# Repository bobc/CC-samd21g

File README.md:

CC-samd21g Breakout Board
========================================

The CC-SAMD21 Breakout Board is breakout for the Atmel ATSAMD21G18 with prototyping area.  
This board shape is dirfferent from Arduino UNO or Zero, but it has Arduino Uno V3 style headers.  
There are only the minimal set of parts for running microcontroller. When you make your own circuit boards, this board might be helpful.

### Some highlights of the CC-samd21g Breakout Board:
 1. Main core: [ATSAMD21G18](http://www.atmel.com/devices/ATSAMD21G18A.aspx)
 2. Volatage regulator can be mounted in the extra prototyping area.
 3. Prototyping area 43.94mm(1730mil) x 53.34mm(2100mil)
 4. Measures 99.82mm(3930mil) x 53.34mm(2100mil)

Repository Contents
-------------------
* **/Hardware** - All Eagle design files (.brd, .sch)
* **/Software** - Software files for this hardware

Description(Pin Interfaces)
-------------------

### CN1 Pin Descriptions:
This connector is for Flashing a program microcontroller.
If you change BOOT MODE, To be selected BOOT MODE before connecting the power supply.  
And also, Communicate with SMA21G using "Serial" function.
- **VCC:** Restrictly 3.3VDC.
- **TX:** PB22 used as UART TX.
- **RX:** PB23 used as UART RX.
- **GND:** GND.
- **BOOT MODE:** Connected to "PA13" H:Flash boot(normally) L:UART download

If you are interested in more useful uart module, please see the [General Serial Communication Board](https://github.com/NaoNaoMe/General-Serial-Communication-Board).

### CN2 Pin Descriptions:
This connector is as power supply.
You can mount a voltage regulator in the extra prototyping area near the connector.
- **VIN:** Depending on the voltage regulator requirements.
- **GND:** GND.

How to burn bootloader and upload sketch
-------------------
See [this page](BurnBootloader.md)

License
-------------------
The repository is released under [Creative Commons ShareAlike 4.0 International](https://creativecommons.org/licenses/by-sa/4.0/).

Distributed as-is; no warranty is given.

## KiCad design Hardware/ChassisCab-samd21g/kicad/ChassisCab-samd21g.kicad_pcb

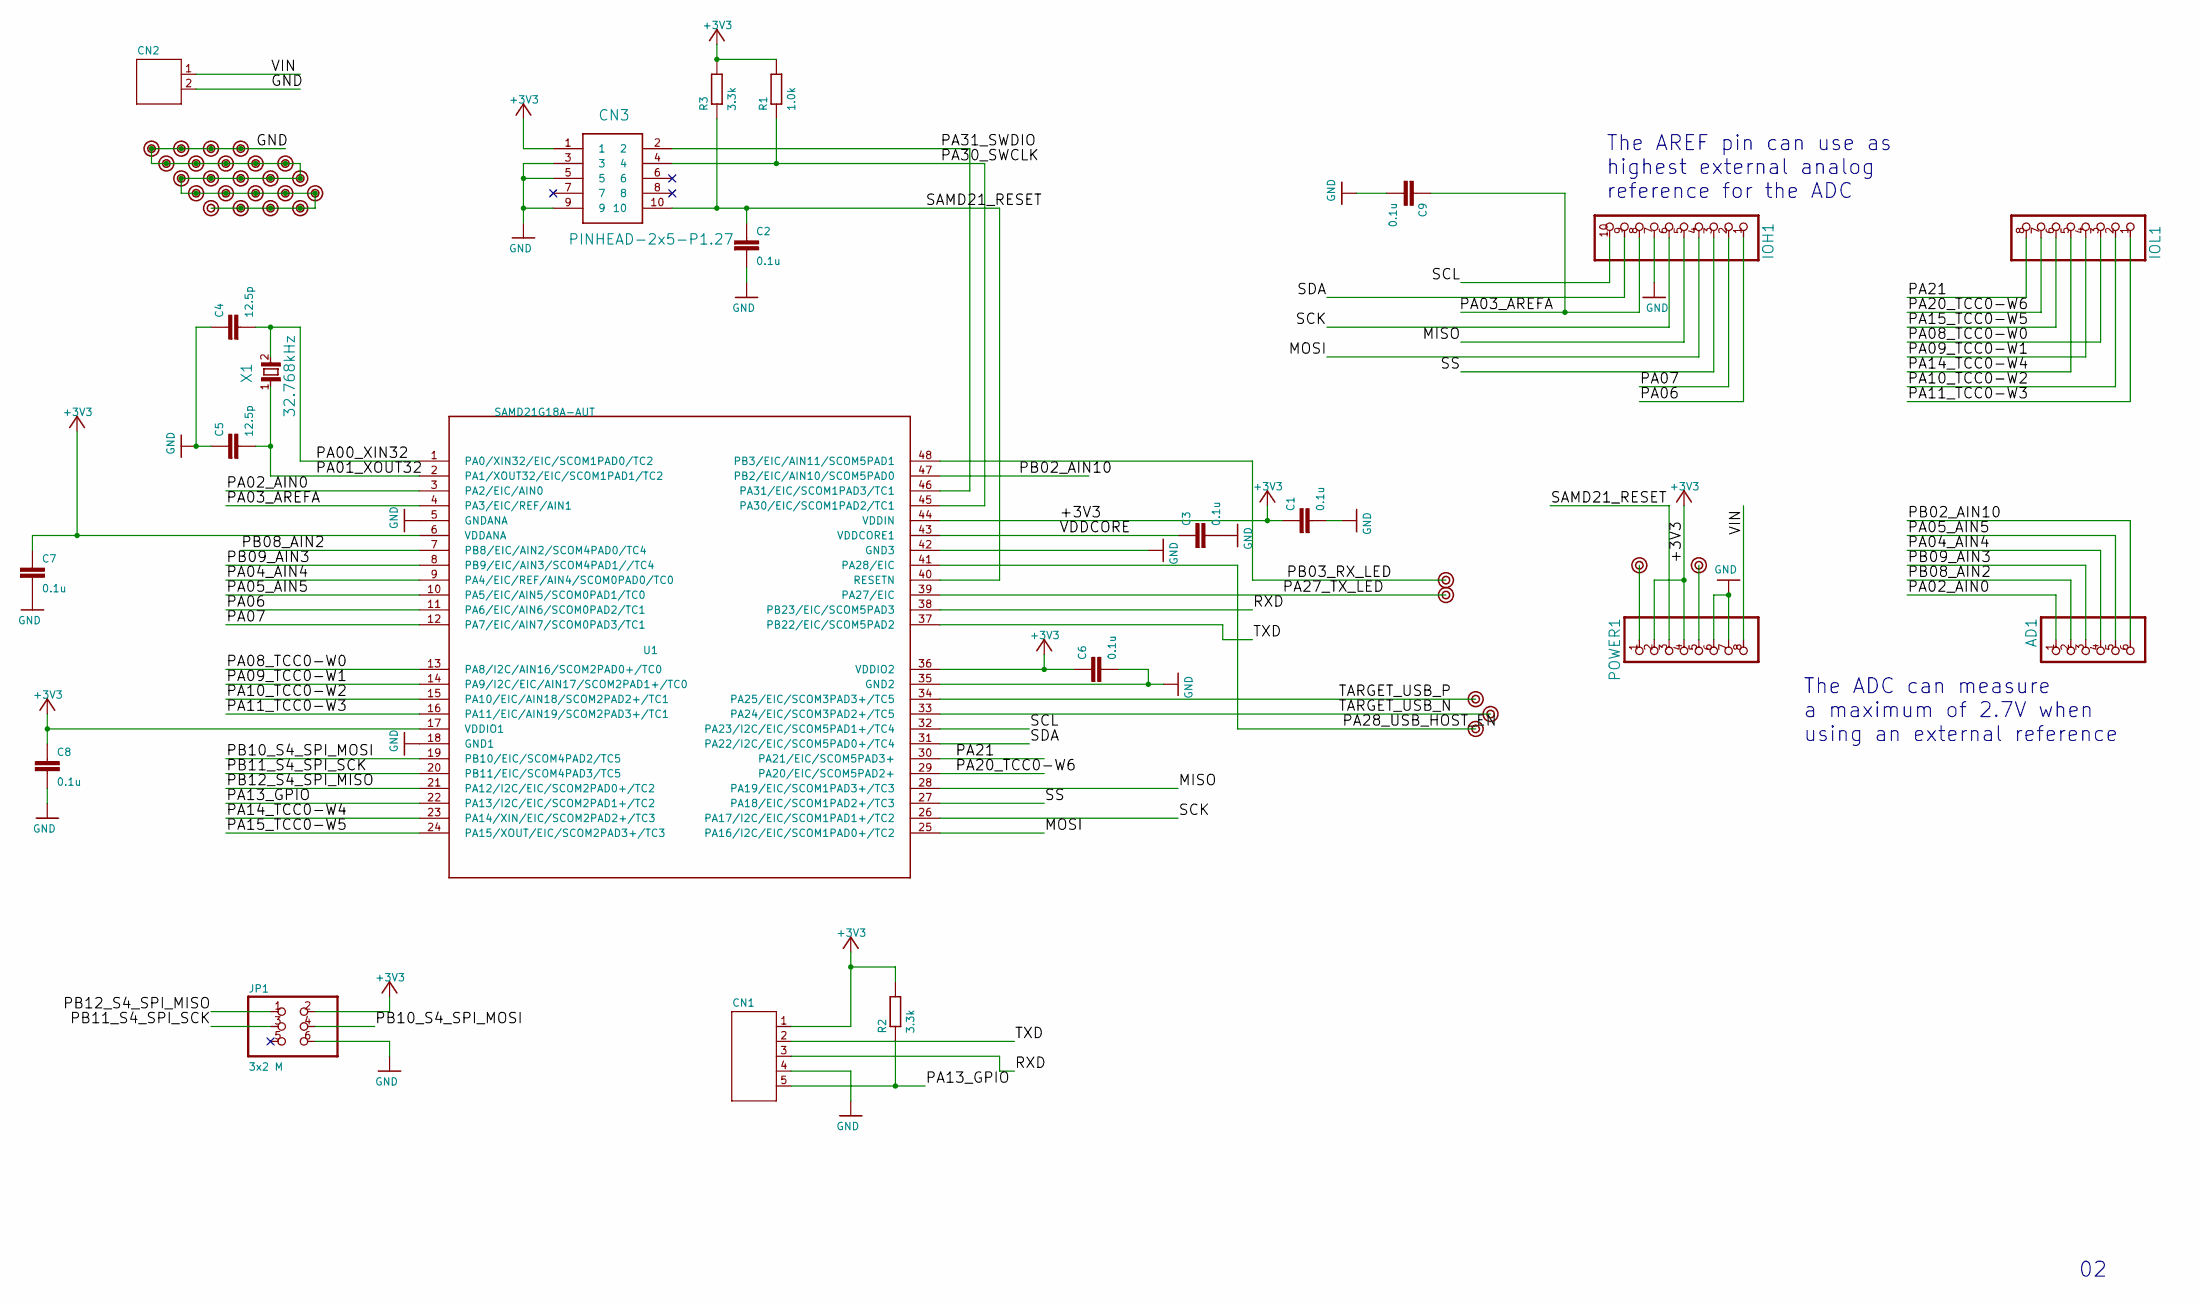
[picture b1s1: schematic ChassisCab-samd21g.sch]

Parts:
AD1: 6x1F-H8.5; 1X06
C1, C2, C3, C6, C7, C8, C9: 0.1u; C0603
C4, C5: 12.5p; C0603
CN1: S5B-PH
CN2: S2B-XH
CN3: PINHEAD-2x5-P1.27; SHF-105-01-X-D-SM
IOH1: 10x1F-H8.5; 1X10
IOL1: 8x1F-H8.5; 1X08
JP1: 3x2 M; 2X03
POWER1: 8x1F-H8.5; 1X08
R1: 1.0k; R0603
R2, R3: 3.3k; R0603
U1: SAMD21G18A-AUT; TQFP48
U$1, U$2, U$3, U$4, U$6, U$7, U$8, U$9, U$10, U$11, U$12, U$13, U$14, U$15, U$16, U$17, U$18, U$19, U$20, U$21, U$22, U$23, U$24, U$25, U$26, U$27, U$28, U$29, U$30, U$31: PAD
X1: 32.768kHz; FC-135

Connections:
+3V3: C1.1, C6.1, C7.1, C8.1, CN1.1, CN3.1, JP1.2, POWER1.2, POWER1.4, R1.2, R2.2, R3.2, U1.6 (VDDANA), U1.17 (VDDIO1), U1.36 (VDDIO2), U1.44 (VDDIN)
GND: C1.2, C2.2, C3.2, C4.1, C5.1, C6.2, C7.2, C8.2, C9.2, CN1.4, CN2.2, CN3.3, CN3.5, CN3.9, IOH1.7, JP1.6, POWER1.6, POWER1.7, U1.5 (GNDANA), U1.18 (GND1), U1.35 (GND2), U1.42 (GND3), U$2.1, U$8.1, U$9.1, U$10.1, U$11.1, U$12.1, U$13.1, U$14.1, U$15.1, U$16.1, U$17.1, U$18.1, U$19.1, U$20.1, U$21.1, U$22.1, U$23.1, U$24.1, U$25.1, U$26.1, U$27.1, U$28.1, U$31.1
MISO: IOH1.5, U1.28 (PA19/EIC/SCOM1PAD3+/TC3)
MOSI: IOH1.4, U1.25 (PA16/I2C/EIC/SCOM1PAD0+/TC2)
unnamed: POWER1.1, U$29.1
unnamed: POWER1.5, U$30.1
PA00_XIN32: C4.2, U1.1 (PA0/XIN32/EIC/SCOM1PAD0/TC2), X1.2
PA01_XOUT32: C5.2, U1.2 (PA1/XOUT32/EIC/SCOM1PAD1/TC2), X1.1
PA02_AIN0: AD1.1, U1.3 (PA2/EIC/AIN0)
PA03_AREFA: C9.1, IOH1.8, U1.4 (PA3/EIC/REF/AIN1)
PA04_AIN4: AD1.4, U1.9 (PA4/EIC/REF/AIN4/SCOM0PAD0/TC0)
PA05_AIN5: AD1.5, U1.10 (PA5/EIC/AIN5/SCOM0PAD1/TC0)
PA06: IOH1.1, U1.11 (PA6/EIC/AIN6/SCOM0PAD2/TC1)
PA07: IOH1.2, U1.12 (PA7/EIC/AIN7/SCOM0PAD3/TC1)
PA08_TCC0-W0: IOL1.3, U1.13 (PA8/I2C/AIN16/SCOM2PAD0+/TC0)
PA09_TCC0-W1: IOL1.4, U1.14 (PA9/I2C/EIC/AIN17/SCOM2PAD1+/TC0)
PA10_TCC0-W2: IOL1.2, U1.15 (PA10/EIC/AIN18/SCOM2PAD2+/TC1)
PA11_TCC0-W3: IOL1.1, U1.16 (PA11/EIC/AIN19/SCOM2PAD3+/TC1)
PA13_GPIO: CN1.5, R2.1, U1.22 (PA13/I2C/EIC/SCOM2PAD1+/TC2)
PA14_TCC0-W4: IOL1.5, U1.23 (PA14/XIN/EIC/SCOM2PAD2+/TC3)
PA15_TCC0-W5: IOL1.6, U1.24 (PA15/XOUT/EIC/SCOM2PAD3+/TC3)
PA20_TCC0-W6: IOL1.7, U1.29 (PA20/EIC/SCOM5PAD2+)
PA21: IOL1.8, U1.30 (PA21/EIC/SCOM5PAD3+)
PA27_TX_LED: U1.39 (PA27/EIC), U$4.1
PA28_USB_HOST_EN: U1.41 (PA28/EIC), U$3.1
PA30_SWCLK: CN3.4, R1.1, U1.45 (PA30/EIC/SCOM1PAD2/TC1)
PA31_SWDIO: CN3.2, U1.46 (PA31/EIC/SCOM1PAD3/TC1)
PB02_AIN10: AD1.6, U1.47 (PB2/EIC/AIN10/SCOM5PAD0)
PB03_RX_LED: U1.48 (PB3/EIC/AIN11/SCOM5PAD1), U$1.1
PB08_AIN2: AD1.2, U1.7 (PB8/EIC/AIN2/SCOM4PAD0/TC4)
PB09_AIN3: AD1.3, U1.8 (PB9/EIC/AIN3/SCOM4PAD1//TC4)
PB10_S4_SPI_MOSI: JP1.4, U1.19 (PB10/EIC/SCOM4PAD2/TC5)
PB11_S4_SPI_SCK: JP1.3, U1.20 (PB11/EIC/SCOM4PAD3/TC5)
PB12_S4_SPI_MISO: JP1.1, U1.21 (PA12/I2C/EIC/SCOM2PAD0+/TC2)
RXD: CN1.3, U1.38 (PB23/EIC/SCOM5PAD3)
SAMD21_RESET: C2.1, CN3.10, POWER1.3, R3.1, U1.40 (RESETN)
SCK: IOH1.6, U1.26 (PA17/I2C/EIC/SCOM1PAD1+/TC2)
SCL: IOH1.10, U1.32 (PA23/I2C/EIC/SCOM5PAD1+/TC4)
SDA: IOH1.9, U1.31 (PA22/I2C/EIC/SCOM5PAD0+/TC4)
SS: IOH1.3, U1.27 (PA18/EIC/SCOM1PAD2+/TC3)
TARGET_USB_N: U1.33 (PA24/EIC/SCOM3PAD2+/TC5), U$7.1
TARGET_USB_P: U1.34 (PA25/EIC/SCOM3PAD3+/TC5), U$6.1
TXD: CN1.2, U1.37 (PB22/EIC/SCOM5PAD2)
VDDCORE: C3.1, U1.43 (VDDCORE1)
VIN: CN2.1, POWER1.8

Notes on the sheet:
The ADC can measure a maximum of 2.7V when using an external reference
The AREF pin can use as highest external analog reference for the ADC

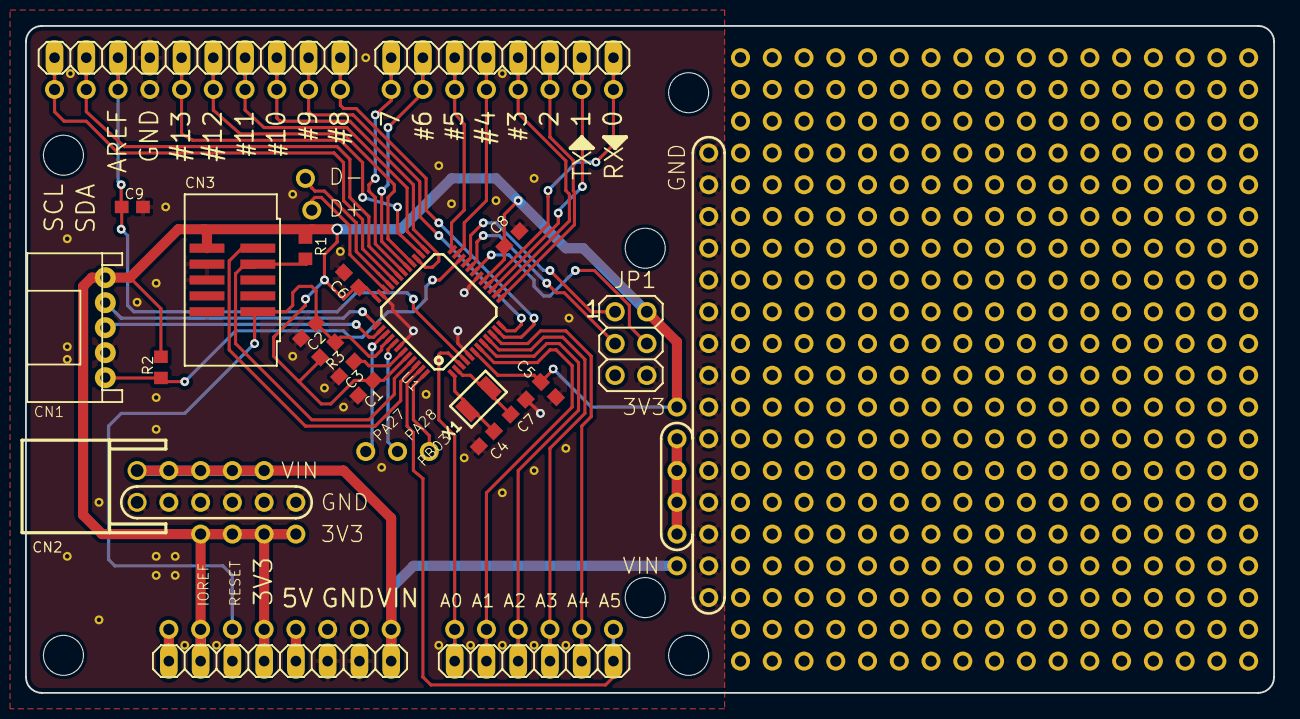
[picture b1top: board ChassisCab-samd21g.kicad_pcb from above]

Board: 2 copper layers, 99.8 x 53.3 mm, 480 parts (0 on the bottom side), 45 nets.

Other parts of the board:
@HOLE1: @HOLE1
@HOLE2: @HOLE2
@HOLE3: @HOLE3
@HOLE4: @HOLE4
@HOLE5: @HOLE5
@HOLE6: @HOLE6
@V1: @V1
@V2: @V2
@V3: @V3
@V4: @V4
@V5: @V5
@V6: @V6
@V7: @V7
@V8: @V8
@V9: @V9
@V10: @V10
@V11: @V11
@V12: @V12
@V13: @V13
@V14: @V14
@V15: @V15
@V16: @V16
@V17: @V17
@V18: @V18
@V19: @V19
@V20: @V20
@V21: @V21
@V22: @V22
@V23: @V23
@V24: @V24
@V25: @V25
@V26: @V26
@V27: @V27
@V28: @V28
@V29: @V29
@V30: @V30
@V31: @V31
@V32: @V32
@V33: @V33
@V34: @V34
@V35: @V35
@V36: @V36
@V37: @V37
@V38: @V38
@V39: @V39
@V40: @V40
@V41: @V41
@V42: @V42
@V43: @V43
@V44: @V44
@V45: @V45
@V46: @V46
@V47: @V47
@V48: @V48
@V49: @V49
@V50: @V50
@V51: @V51
@V52: @V52
@V53: @V53
@V54: @V54
@V55: @V55
@V56: @V56
@V57: @V57
@V58: @V58
@V59: @V59
@V60: @V60
@V61: @V61
@V62: @V62
@V63: @V63
@V64: @V64
@V65: @V65
@V66: @V66
@V67: @V67
@V68: @V68
@V69: @V69
@V70: @V70
@V71: @V71
@V72: @V72
@V73: @V73
@V74: @V74
@V75: @V75
@V76: @V76
@V77: @V77
@V78: @V78
@V79: @V79
@V80: @V80
@V81: @V81
@V82: @V82
@V83: @V83
@V84: @V84
@V85: @V85
@V86: @V86
@V87: @V87
@V88: @V88
@V89: @V89
@V90: @V90
@V91: @V91
@V92: @V92
@V93: @V93
@V94: @V94
@V95: @V95
@V96: @V96
@V97: @V97
@V98: @V98
@V99: @V99
@V100: @V100
@V101: @V101
@V102: @V102
@V103: @V103
@V104: @V104
@V105: @V105
@V106: @V106
@V107: @V107
@V108: @V108
@V109: @V109
@V110: @V110
@V111: @V111
@V112: @V112
@V113: @V113
@V114: @V114
@V115: @V115
@V116: @V116
@V117: @V117
@V118: @V118
@V119: @V119
@V120: @V120
@V121: @V121
@V122: @V122
@V123: @V123
@V124: @V124
@V125: @V125
@V126: @V126
@V127: @V127
@V128: @V128
@V129: @V129
@V130: @V130
@V131: @V131
@V132: @V132
@V133: @V133
@V134: @V134
@V135: @V135
@V136: @V136
@V137: @V137
@V138: @V138
@V139: @V139
@V140: @V140
@V141: @V141
@V142: @V142
@V143: @V143
@V144: @V144
@V145: @V145
@V146: @V146
@V147: @V147
@V148: @V148
@V149: @V149
@V150: @V150
@V151: @V151
@V152: @V152
@V153: @V153
@V154: @V154
@V155: @V155
@V156: @V156
@V157: @V157
@V158: @V158
@V159: @V159
@V160: @V160
@V161: @V161
@V162: @V162
@V163: @V163
@V164: @V164
@V165: @V165
@V166: @V166
@V167: @V167
@V168: @V168
@V169: @V169
@V170: @V170
@V171: @V171
@V172: @V172
@V173: @V173
@V174: @V174
@V175: @V175
@V176: @V176
@V177: @V177
@V178: @V178
@V179: @V179
@V180: @V180
@V181: @V181
@V182: @V182
@V183: @V183
@V184: @V184
@V185: @V185
@V186: @V186
@V187: @V187
@V188: @V188
@V189: @V189
@V190: @V190
@V191: @V191
@V192: @V192
@V193: @V193
@V194: @V194
@V195: @V195
@V196: @V196
@V197: @V197
@V198: @V198
@V199: @V199
@V200: @V200
@V201: @V201
@V202: @V202
@V203: @V203
@V204: @V204
@V205: @V205
@V206: @V206
@V207: @V207
@V208: @V208
@V209: @V209
@V210: @V210
@V211: @V211
@V212: @V212
@V213: @V213
@V214: @V214
@V215: @V215
@V216: @V216
@V217: @V217
@V218: @V218
@V219: @V219
@V220: @V220
@V221: @V221
@V222: @V222
@V223: @V223
@V224: @V224
@V225: @V225
@V226: @V226
@V227: @V227
@V228: @V228
@V229: @V229
@V230: @V230
@V231: @V231
@V232: @V232
@V233: @V233
@V234: @V234
@V235: @V235
@V236: @V236
@V237: @V237
@V238: @V238
@V239: @V239
@V240: @V240
@V241: @V241
@V242: @V242
@V243: @V243
@V244: @V244
@V245: @V245
@V246: @V246
@V247: @V247
@V248: @V248
@V249: @V249
@V250: @V250
@V251: @V251
@V252: @V252
@V253: @V253
@V254: @V254
@V255: @V255
@V256: @V256
@V257: @V257
@V258: @V258
@V259: @V259
@V260: @V260
@V261: @V261
@V262: @V262
@V263: @V263
@V264: @V264
@V265: @V265
@V266: @V266
@V267: @V267
@V268: @V268
@V269: @V269
@V270: @V270
@V271: @V271
@V272: @V272
@V273: @V273
@V274: @V274
@V275: @V275
@V276: @V276
@V277: @V277
@V278: @V278
@V279: @V279
@V280: @V280
@V281: @V281
@V282: @V282
@V283: @V283
@V284: @V284
@V285: @V285
@V286: @V286
@V287: @V287
@V288: @V288
@V289: @V289
@V290: @V290
@V291: @V291
@V292: @V292
@V293: @V293
@V294: @V294
@V295: @V295
@V296: @V296
@V297: @V297
@V298: @V298
@V299: @V299
@V300: @V300
@V301: @V301
@V302: @V302
@V303: @V303
@V304: @V304
@V305: @V305
@V306: @V306
@V307: @V307
@V308: @V308
@V309: @V309
@V310: @V310
@V311: @V311
@V312: @V312
@V313: @V313
@V314: @V314
@V315: @V315
@V316: @V316
@V317: @V317
@V318: @V318
@V319: @V319
@V320: @V320
@V321: @V321
@V322: @V322
@V323: @V323
@V324: @V324
@V325: @V325
@V326: @V326
@V327: @V327
@V328: @V328
@V329: @V329
@V330: @V330
@V331: @V331
@V332: @V332
@V333: @V333
@V334: @V334
@V335: @V335
@V336: @V336
@V337: @V337
@V338: @V338
@V339: @V339
@V340: @V340
@V341: @V341
@V342: @V342
@V343: @V343
@V344: @V344
@V345: @V345
@V346: @V346
@V347: @V347
@V348: @V348
@V349: @V349
@V350: @V350
@V351: @V351
@V352: @V352
@V353: @V353
@V354: @V354
@V355: @V355
@V356: @V356
@V357: @V357
@V358: @V358
@V359: @V359
@V360: @V360
@V361: @V361
@V362: @V362
@V363: @V363
@V364: @V364
@V365: @V365
@V366: @V366
@V367: @V367
@V368: @V368
@V369: @V369
@V370: @V370
@V371: @V371
@V372: @V372
@V373: @V373
@V374: @V374
@V375: @V375
@V376: @V376
@V377: @V377
@V378: @V378
@V379: @V379
@V380: @V380
@V381: @V381
@V382: @V382
@V383: @V383
@V384: @V384
@V385: @V385
@V386: @V386
@V387: @V387
@V388: @V388
@V389: @V389
@V390: @V390
@V391: @V391
@V392: @V392
@V393: @V393
@V394: @V394
@V395: @V395
@V396: @V396
@V397: @V397
@V398: @V398
@V399: @V399
@V400: @V400
@V401: @V401
@V402: @V402
@V403: @V403
@V404: @V404
@V405: @V405
@V406: @V406
@V407: @V407
@V408: @V408
@V409: @V409
@V410: @V410
@V411: @V411
@V412: @V412
@V413: @V413
@V414: @V414
@V415: @V415
@V416: @V416
@V417: @V417
@V418: @V418
@V419: @V419
@V420: @V420
@V421: @V421
@V422: @V422

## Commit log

2017-03-31 add files
2017-05-13 typo
2017-06-13 Conversion to KiCad

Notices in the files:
parts and their libraries:
jst: Copyright (C) 2016, Naoya Imai
